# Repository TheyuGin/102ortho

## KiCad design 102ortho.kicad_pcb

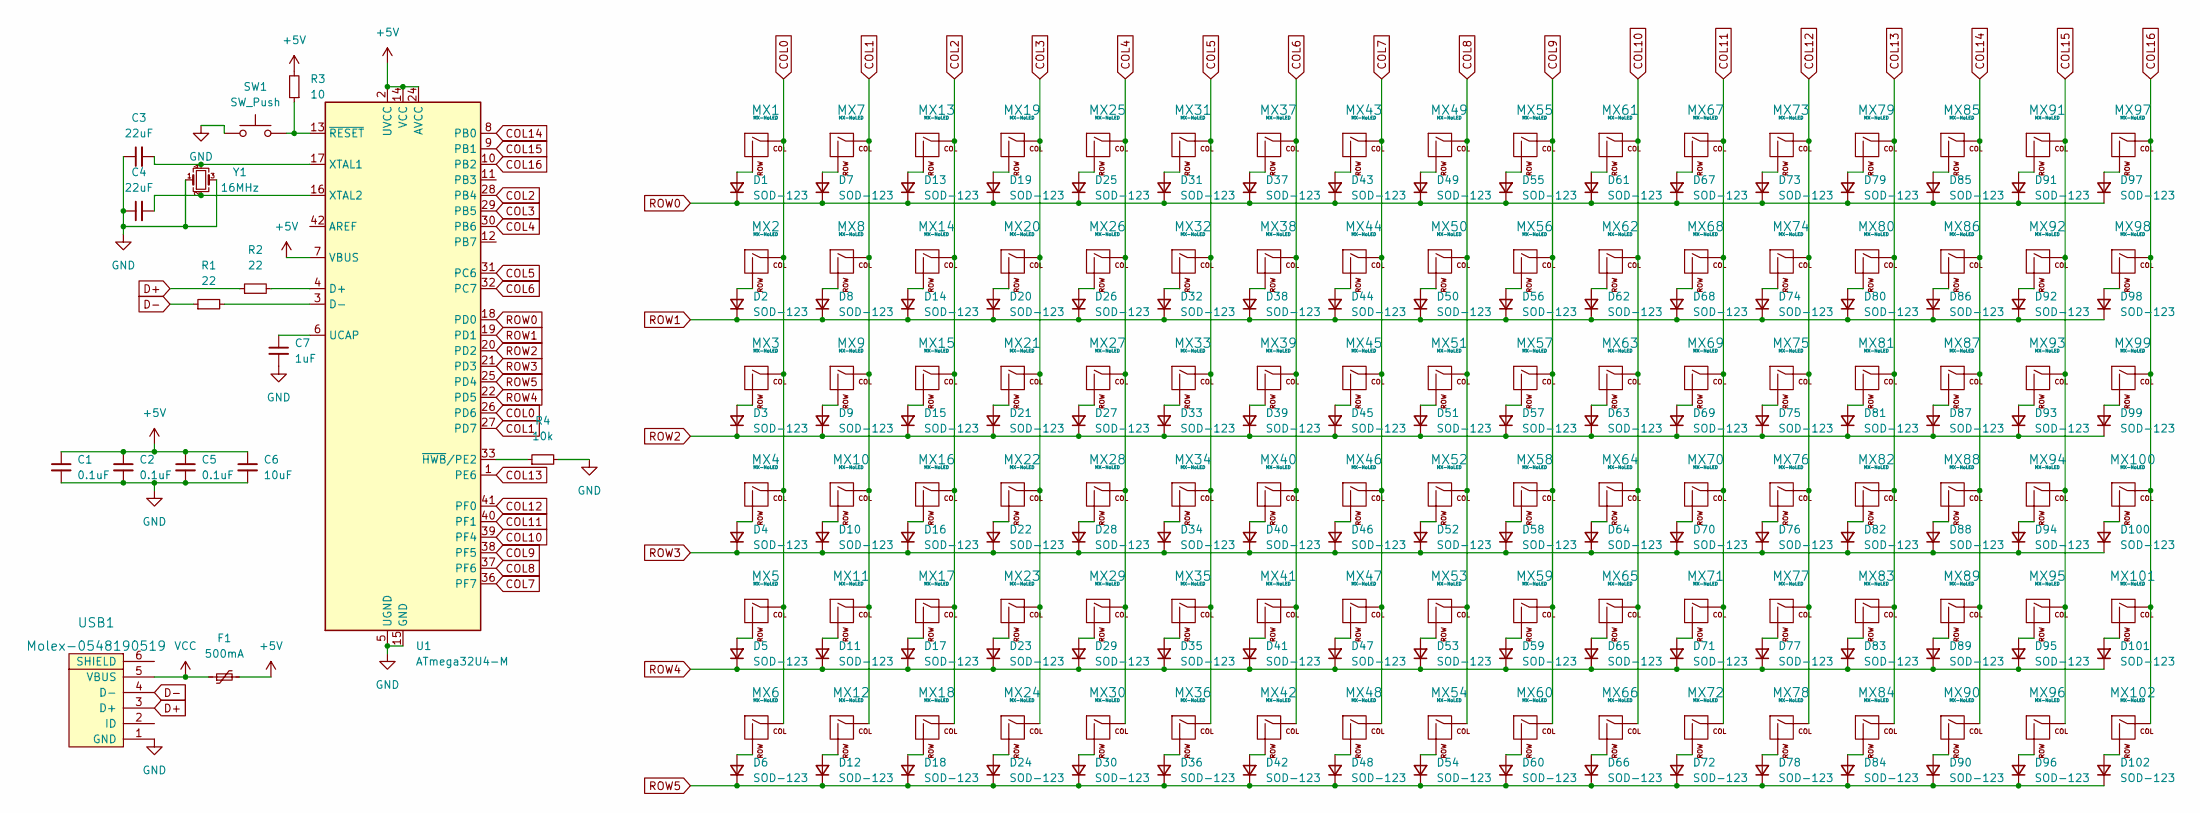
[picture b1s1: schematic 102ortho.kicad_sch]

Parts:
C1, C2, C5: 0.1uF; C_0805_2012Metric
C3, C4: 22uF; C_0805_2012Metric
C6: 10uF; C_0805_2012Metric
C7: 1uF; C_0805_2012Metric
D1, D2, D3, D4, D5, D6, D7, D8, D9, D10, D11, D12, D13, D14, D15, D16, D17, D18, D19, D20, D21, D22, D23, D24, D25, D26, D27, D28, D29, D30, D31, D32, D33, D34, D35, D36, D37, D38, D39, D40, D41, D42, D43, D44, D45, D46, D47, D48, D49, D50, D51, D52, D53, D54, D55, D56, D57, D58, D59, D60, D61, D62, D63, D64, D65, D66, D67, D68, D69, D70, D71, D72, D73, D74, D75, D76, D77, D78, D79, D80, D81, D82, D83, D84, D85, D86, D87, D88, D89, D90, D91, D92, D93, D94, D95, D96, D97, D98, D99, D100, D101, D102: SOD-123; D_SOD-123
F1: 500mA; Fuse_1206_3216Metric
MX1, MX2, MX3, MX4, MX5, MX6, MX7, MX8, MX9, MX10, MX11, MX12, MX13, MX14, MX15, MX16, MX17, MX18, MX19, MX20, MX21, MX22, MX23, MX24, MX25, MX26, MX27, MX28, MX29, MX30, MX31, MX32, MX33, MX34, MX35, MX36, MX37, MX38, MX39, MX40, MX41, MX42, MX43, MX44, MX45, MX46, MX47, MX48, MX49, MX50, MX51, MX52, MX53, MX54, MX55, MX56, MX57, MX58, MX59, MX60, MX61, MX62, MX63, MX64, MX65, MX66, MX67, MX68, MX69, MX70, MX71, MX72, MX73, MX74, MX75, MX76, MX77, MX78, MX79, MX80, MX81, MX82, MX83, MX84, MX85, MX86, MX87, MX88, MX89, MX90, MX91, MX92, MX93, MX94, MX95, MX96, MX97, MX98, MX99, MX100, MX101, MX102: MX-NoLED; MXOnly-1U-Hotswap-Antishear
R1, R2: 22; R_1210_3225Metric
R3: 10; R_1210_3225Metric
R4: 10k; R_1210_3225Metric
SW1: SW_Push; SKQG-1155865
U1: ATmega32U4-M; TQFP-44_10x10mm_P0.8mm
USB1: Molex-0548190519; Molex-0548190589
Y1: 16MHz; Crystal_SMD_3225-4Pin_3.2x2.5mm

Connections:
+5V: C1.1, C2.1, C5.1, C6.1, F1.2, R3.2, U1.2 (UVCC), U1.7 (VBUS), U1.14 (VCC), U1.24 (AVCC), U1.34 (VCC), U1.44 (AVCC)
COL0: MX1.1 (COL), MX2.1 (COL), MX3.1 (COL), MX4.1 (COL), MX5.1 (COL), MX6.1 (COL), U1.26 (PD6)
COL1: MX7.1 (COL), MX8.1 (COL), MX9.1 (COL), MX10.1 (COL), MX11.1 (COL), MX12.1 (COL), U1.27 (PD7)
COL2: MX13.1 (COL), MX14.1 (COL), MX15.1 (COL), MX16.1 (COL), MX17.1 (COL), MX18.1 (COL), U1.28 (PB4)
COL3: MX19.1 (COL), MX20.1 (COL), MX21.1 (COL), MX22.1 (COL), MX23.1 (COL), MX24.1 (COL), U1.29 (PB5)
COL4: MX25.1 (COL), MX26.1 (COL), MX27.1 (COL), MX28.1 (COL), MX29.1 (COL), MX30.1 (COL), U1.30 (PB6)
COL5: MX31.1 (COL), MX32.1 (COL), MX33.1 (COL), MX34.1 (COL), MX35.1 (COL), MX36.1 (COL), U1.31 (PC6)
COL6: MX37.1 (COL), MX38.1 (COL), MX39.1 (COL), MX40.1 (COL), MX41.1 (COL), MX42.1 (COL), U1.32 (PC7)
COL7: MX43.1 (COL), MX44.1 (COL), MX45.1 (COL), MX46.1 (COL), MX47.1 (COL), MX48.1 (COL), U1.36 (PF7)
COL8: MX49.1 (COL), MX50.1 (COL), MX51.1 (COL), MX52.1 (COL), MX53.1 (COL), MX54.1 (COL), U1.37 (PF6)
COL9: MX55.1 (COL), MX56.1 (COL), MX57.1 (COL), MX58.1 (COL), MX59.1 (COL), MX60.1 (COL), U1.38 (PF5)
COL10: MX61.1 (COL), MX62.1 (COL), MX63.1 (COL), MX64.1 (COL), MX65.1 (COL), MX66.1 (COL), U1.39 (PF4)
COL11: MX67.1 (COL), MX68.1 (COL), MX69.1 (COL), MX70.1 (COL), MX71.1 (COL), MX72.1 (COL), U1.40 (PF1)
COL12: MX73.1 (COL), MX74.1 (COL), MX75.1 (COL), MX76.1 (COL), MX77.1 (COL), MX78.1 (COL), U1.41 (PF0)
COL13: MX79.1 (COL), MX80.1 (COL), MX81.1 (COL), MX82.1 (COL), MX83.1 (COL), MX84.1 (COL), U1.1 (PE6)
COL14: MX85.1 (COL), MX86.1 (COL), MX87.1 (COL), MX88.1 (COL), MX89.1 (COL), MX90.1 (COL), U1.8 (PB0)
COL15: MX91.1 (COL), MX92.1 (COL), MX93.1 (COL), MX94.1 (COL), MX95.1 (COL), MX96.1 (COL), U1.9 (PB1)
COL16: MX97.1 (COL), MX98.1 (COL), MX99.1 (COL), MX100.1 (COL), MX101.1 (COL), MX102.1 (COL), U1.10 (PB2)
D+: R2.1, USB1.3 (D+)
D-: R1.1, USB1.4 (D-)
GND: C1.2, C2.2, C3.1, C4.1, C5.2, C6.2, C7.2, R4.2, SW1.1, U1.5 (UGND), U1.15 (GND), U1.23 (GND), U1.35 (GND), U1.43 (GND), U1.45 (GND), USB1.1 (GND), Y1.1, Y1.3
unnamed: C3.2, U1.17 (XTAL1), Y1.4
unnamed: C4.2, U1.16 (XTAL2), Y1.2
unnamed: C7.1, U1.6 (UCAP)
unnamed: D1.2 (A), MX1.2 (ROW)
unnamed: D2.2 (A), MX2.2 (ROW)
unnamed: D3.2 (A), MX3.2 (ROW)
unnamed: D4.2 (A), MX4.2 (ROW)
unnamed: D5.2 (A), MX5.2 (ROW)
unnamed: D6.2 (A), MX6.2 (ROW)
unnamed: D7.2 (A), MX7.2 (ROW)
unnamed: D8.2 (A), MX8.2 (ROW)
unnamed: D9.2 (A), MX9.2 (ROW)
unnamed: D10.2 (A), MX10.2 (ROW)
unnamed: D11.2 (A), MX11.2 (ROW)
unnamed: D12.2 (A), MX12.2 (ROW)
unnamed: D13.2 (A), MX13.2 (ROW)
unnamed: D14.2 (A), MX14.2 (ROW)
unnamed: D15.2 (A), MX15.2 (ROW)
unnamed: D16.2 (A), MX16.2 (ROW)
unnamed: D17.2 (A), MX17.2 (ROW)
unnamed: D18.2 (A), MX18.2 (ROW)
unnamed: D19.2 (A), MX19.2 (ROW)
unnamed: D20.2 (A), MX20.2 (ROW)
unnamed: D21.2 (A), MX21.2 (ROW)
unnamed: D22.2 (A), MX22.2 (ROW)
unnamed: D23.2 (A), MX23.2 (ROW)
unnamed: D24.2 (A), MX24.2 (ROW)
unnamed: D25.2 (A), MX25.2 (ROW)
unnamed: D26.2 (A), MX26.2 (ROW)
unnamed: D27.2 (A), MX27.2 (ROW)
unnamed: D28.2 (A), MX28.2 (ROW)
unnamed: D29.2 (A), MX29.2 (ROW)
unnamed: D30.2 (A), MX30.2 (ROW)
unnamed: D31.2 (A), MX31.2 (ROW)
unnamed: D32.2 (A), MX32.2 (ROW)
unnamed: D33.2 (A), MX33.2 (ROW)
unnamed: D34.2 (A), MX34.2 (ROW)
unnamed: D35.2 (A), MX35.2 (ROW)
unnamed: D36.2 (A), MX36.2 (ROW)
unnamed: D37.2 (A), MX37.2 (ROW)
unnamed: D38.2 (A), MX38.2 (ROW)
unnamed: D39.2 (A), MX39.2 (ROW)
unnamed: D40.2 (A), MX40.2 (ROW)
unnamed: D41.2 (A), MX41.2 (ROW)
unnamed: D42.2 (A), MX42.2 (ROW)
unnamed: D43.2 (A), MX43.2 (ROW)
unnamed: D44.2 (A), MX44.2 (ROW)
unnamed: D45.2 (A), MX45.2 (ROW)
unnamed: D46.2 (A), MX46.2 (ROW)
unnamed: D47.2 (A), MX47.2 (ROW)
unnamed: D48.2 (A), MX48.2 (ROW)
unnamed: D49.2 (A), MX49.2 (ROW)
unnamed: D50.2 (A), MX50.2 (ROW)
unnamed: D51.2 (A), MX51.2 (ROW)
unnamed: D52.2 (A), MX52.2 (ROW)
unnamed: D53.2 (A), MX53.2 (ROW)
unnamed: D54.2 (A), MX54.2 (ROW)
unnamed: D55.2 (A), MX55.2 (ROW)
unnamed: D56.2 (A), MX56.2 (ROW)
unnamed: D57.2 (A), MX57.2 (ROW)
unnamed: D58.2 (A), MX58.2 (ROW)
unnamed: D59.2 (A), MX59.2 (ROW)
unnamed: D60.2 (A), MX60.2 (ROW)
unnamed: D61.2 (A), MX61.2 (ROW)
unnamed: D62.2 (A), MX62.2 (ROW)
unnamed: D63.2 (A), MX63.2 (ROW)
unnamed: D64.2 (A), MX64.2 (ROW)
unnamed: D65.2 (A), MX65.2 (ROW)
unnamed: D66.2 (A), MX66.2 (ROW)
unnamed: D67.2 (A), MX67.2 (ROW)
unnamed: D68.2 (A), MX68.2 (ROW)
unnamed: D69.2 (A), MX69.2 (ROW)
unnamed: D70.2 (A), MX70.2 (ROW)
unnamed: D71.2 (A), MX71.2 (ROW)
unnamed: D72.2 (A), MX72.2 (ROW)
unnamed: D73.2 (A), MX73.2 (ROW)
unnamed: D74.2 (A), MX74.2 (ROW)
unnamed: D75.2 (A), MX75.2 (ROW)
unnamed: D76.2 (A), MX76.2 (ROW)
unnamed: D77.2 (A), MX77.2 (ROW)
unnamed: D78.2 (A), MX78.2 (ROW)
unnamed: D79.2 (A), MX79.2 (ROW)
unnamed: D80.2 (A), MX80.2 (ROW)
unnamed: D81.2 (A), MX81.2 (ROW)
unnamed: D82.2 (A), MX82.2 (ROW)
unnamed: D83.2 (A), MX83.2 (ROW)
unnamed: D84.2 (A), MX84.2 (ROW)
unnamed: D85.2 (A), MX85.2 (ROW)
unnamed: D86.2 (A), MX86.2 (ROW)
unnamed: D87.2 (A), MX87.2 (ROW)
unnamed: D88.2 (A), MX88.2 (ROW)
unnamed: D89.2 (A), MX89.2 (ROW)
unnamed: D90.2 (A), MX90.2 (ROW)
unnamed: D91.2 (A), MX91.2 (ROW)
unnamed: D92.2 (A), MX92.2 (ROW)
unnamed: D93.2 (A), MX93.2 (ROW)
unnamed: D94.2 (A), MX94.2 (ROW)
unnamed: D95.2 (A), MX95.2 (ROW)
unnamed: D96.2 (A), MX96.2 (ROW)
unnamed: D97.2 (A), MX97.2 (ROW)
unnamed: D98.2 (A), MX98.2 (ROW)
unnamed: D99.2 (A), MX99.2 (ROW)
unnamed: D100.2 (A), MX100.2 (ROW)
unnamed: D101.2 (A), MX101.2 (ROW)
unnamed: D102.2 (A), MX102.2 (ROW)
unnamed: R1.2, U1.3 (D-)
unnamed: R2.2, U1.4 (D+)
unnamed: R3.1, SW1.2, U1.13 (~RESET)
unnamed: R4.1, U1.33 (~HWB/PE2)
ROW0: D1.1 (K), D7.1 (K), D13.1 (K), D19.1 (K), D25.1 (K), D31.1 (K), D37.1 (K), D43.1 (K), D49.1 (K), D55.1 (K), D61.1 (K), D67.1 (K), D73.1 (K), D79.1 (K), D85.1 (K), D91.1 (K), D97.1 (K), U1.18 (PD0)
ROW1: D2.1 (K), D8.1 (K), D14.1 (K), D20.1 (K), D26.1 (K), D32.1 (K), D38.1 (K), D44.1 (K), D50.1 (K), D56.1 (K), D62.1 (K), D68.1 (K), D74.1 (K), D80.1 (K), D86.1 (K), D92.1 (K), D98.1 (K), U1.19 (PD1)
ROW2: D3.1 (K), D9.1 (K), D15.1 (K), D21.1 (K), D27.1 (K), D33.1 (K), D39.1 (K), D45.1 (K), D51.1 (K), D57.1 (K), D63.1 (K), D69.1 (K), D75.1 (K), D81.1 (K), D87.1 (K), D93.1 (K), D99.1 (K), U1.20 (PD2)
ROW3: D4.1 (K), D10.1 (K), D16.1 (K), D22.1 (K), D28.1 (K), D34.1 (K), D40.1 (K), D46.1 (K), D52.1 (K), D58.1 (K), D64.1 (K), D70.1 (K), D76.1 (K), D82.1 (K), D88.1 (K), D94.1 (K), D100.1 (K), U1.21 (PD3)
ROW4: D5.1 (K), D11.1 (K), D17.1 (K), D23.1 (K), D29.1 (K), D35.1 (K), D41.1 (K), D47.1 (K), D53.1 (K), D59.1 (K), D65.1 (K), D71.1 (K), D77.1 (K), D83.1 (K), D89.1 (K), D95.1 (K), D101.1 (K), U1.22 (PD5)
ROW5: D6.1 (K), D12.1 (K), D18.1 (K), D24.1 (K), D30.1 (K), D36.1 (K), D42.1 (K), D48.1 (K), D54.1 (K), D60.1 (K), D66.1 (K), D72.1 (K), D78.1 (K), D84.1 (K), D90.1 (K), D96.1 (K), D102.1 (K), U1.25 (PD4)
VCC: F1.1, USB1.5 (VBUS)

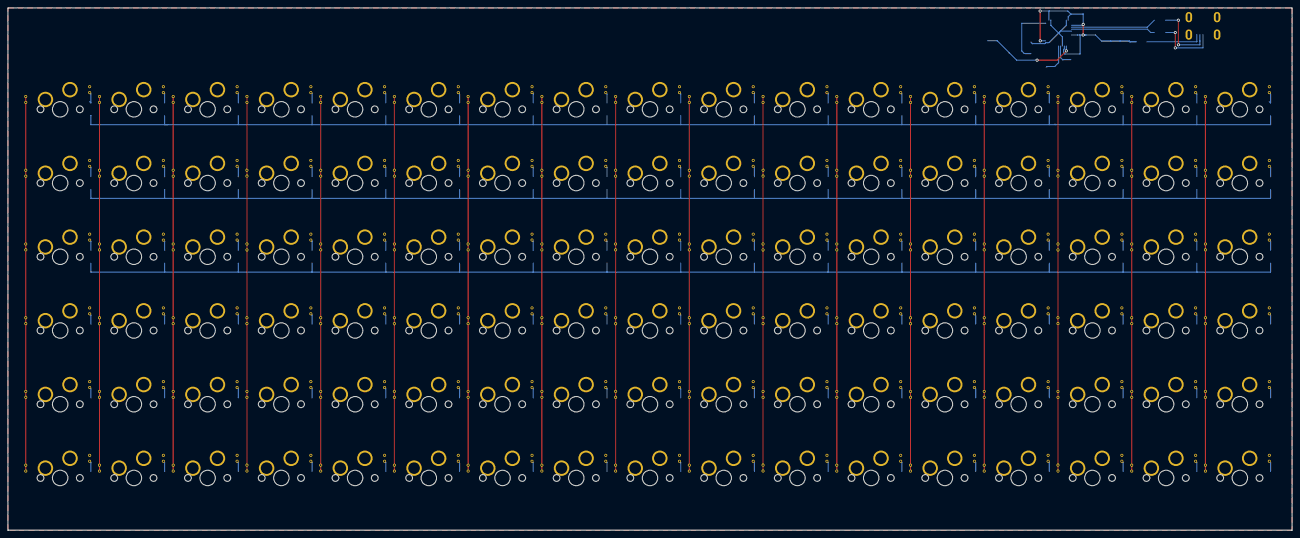
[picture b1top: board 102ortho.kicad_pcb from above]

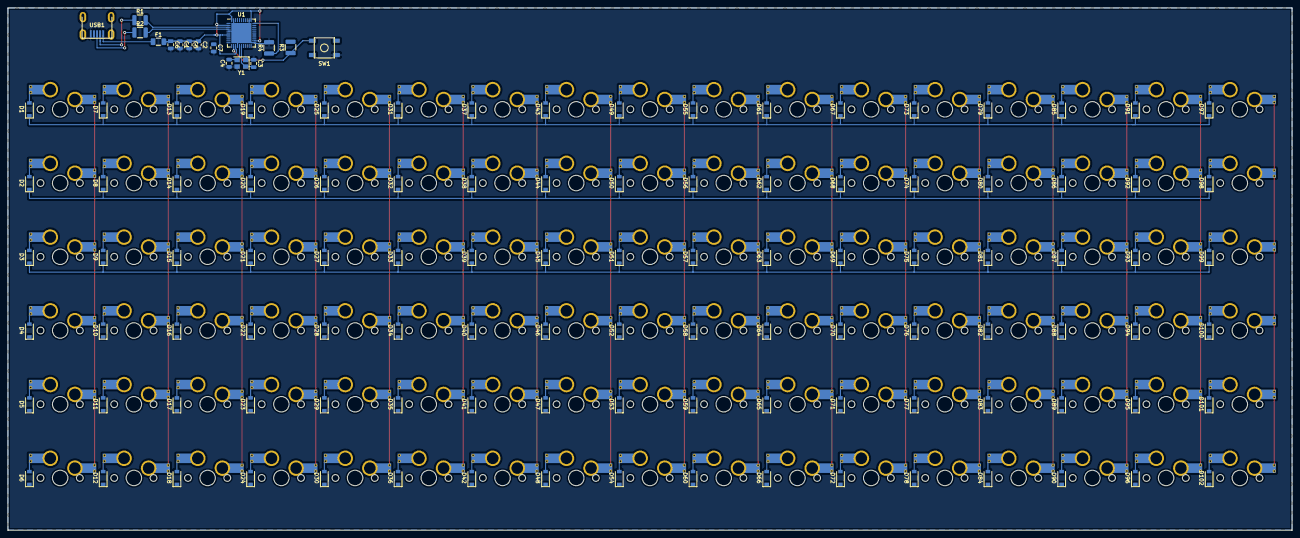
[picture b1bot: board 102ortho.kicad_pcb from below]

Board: 2 copper layers, 331.8 x 134.9 mm, 220 parts (118 on the bottom side), 137 nets.

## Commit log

2022-02-15 initial
